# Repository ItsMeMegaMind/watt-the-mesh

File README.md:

# ⚡ Watt-The-Mesh

> ⚠️ **WORK IN PROGRESS:** This hardware design and PCB layout are currently under active development. Schematics, footprints, and routing are subject to change before the first physical revision is fully tested and verified in the field.

---

**Watt-The-Mesh** is an open-source, ultra-range off-grid Meshtastic relay board. Designed to punch through long distances without dying on you in the field, it combines a high-efficiency power subsystem with a high-power 1W LoRa power amplifier.

### 🛠️ Hardware Specifications
* **MCU:** Nordic nRF52840 (Ultra-low power Bluetooth & System Controller)
* **RF Transceiver:** E22-900M30S (1W / +30dBm SX1262 LoRa module)
* **Power Management:** Integrated solar charging + high-efficiency TPS61022 boost converter for stable 5V delivery during 1W transmission bursts
* **Form Factor:** Compact, single-board design optimized for low EMI and off-grid mast deployment

### 🚧 Project Status
- [x] Power Subsystem & Boost Converter Layout (TPS61022)
- [ ] Solar Charger & Battery Management Integration
- [ ] nRF52840 & E22 Interconnect Routing
- [ ] Board Revision 1.0 Manufacturing & Bench Testing
- [ ] Outdoor Field Range & Solar Endurance Testing

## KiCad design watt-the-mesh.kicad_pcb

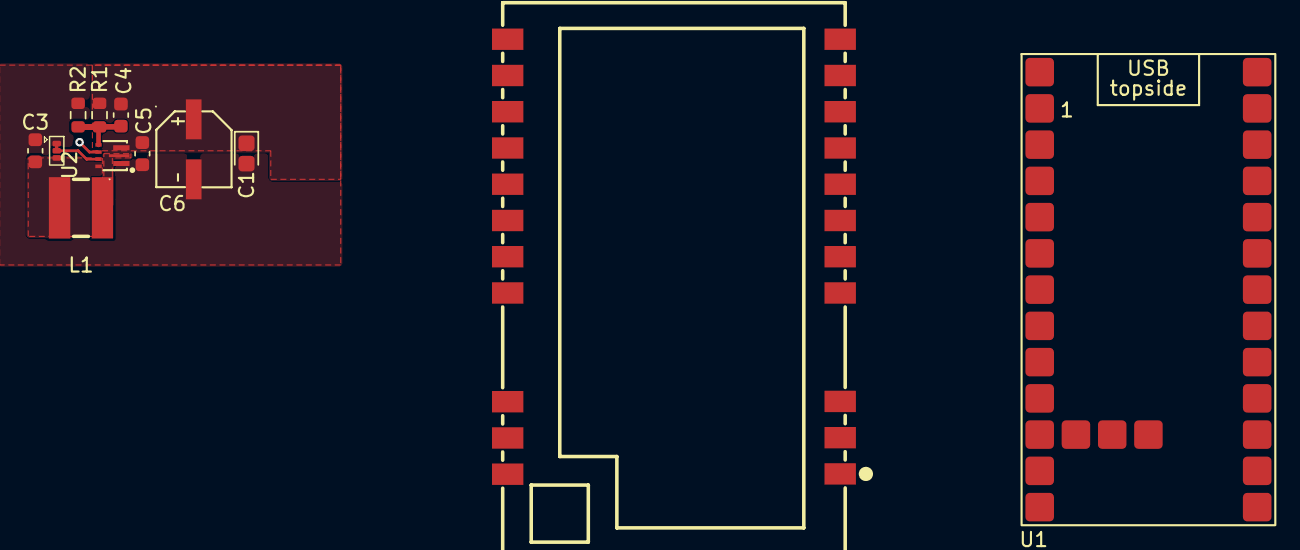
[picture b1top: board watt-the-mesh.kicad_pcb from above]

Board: 2 copper layers, 12 parts (0 on the bottom side), 6 nets.

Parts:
C1: C_Polarized_Small_US; CP_EIA-1608-08_AVX-J
C3: 22uf; C_0603_1608Metric
C4: 10pf; C_0603_1608Metric
C5: 22uF; C_0603_1608Metric
C6: 16SVPG100M; CAP-SMD_BD5.0-L5.3-W5.3-LS6.0-FD
JP2: SolderJumper_3_Bridged12; SolderJumper-3_P1.3mm_Bridged12_RoundedPad
L1: 10uf; IND-SMD_L4.0-W4.0_YSMC0430V
R1: 732K; R_0603_1608Metric
R2: 100K; R_0603_1608Metric
U1: nice_nano; nice_nano_AH_USBup
U2: TPS61022RWUR; VQFN-7_L2.0-W2.0-P0.55-TL_RWU
U3: E22P-915M30S; COMM-SMD_22P-P2.54-L38.5-W24.0_E22-400M33S

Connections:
+5V: C1.1, C4.2, C5.1, C6.1, R1.2, U2.3 (VOUT)
+BATT: C3.1, JP2.3 (B), L1.2, U2.7 (VIN)
GND: C1.2, C3.2, C5.2, C6.2, JP2.1 (A), R2.2, U2.1 (GND)
unnamed: JP2.2 (C), U2.6 (MODE)
unnamed: C4.1, R1.1, R2.1, U2.4 (FB)
unnamed: L1.1, U2.2 (SW)
